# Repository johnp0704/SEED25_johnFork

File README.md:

# The Autonomous Weeding Garden Robot (AWGR)

[User operation video](https://drive.google.com/file/d/1jZLO9X0hrXnLbDT-zOZEFcToG8p_CPjy/view?usp=sharing) <br/>
There are a number of folders in this repo to help develop the AWGR. There are README files in each directory with further clarification of individual files. 
## RC Control 
Guide on how to setup RC mode for the robot. Scripts for microcontrollers.
## automation 
Guide for the robots autonomy. Includes information on the script that runs on startup, and the script itself. 
## drawings
.png files of all the parts that were either 3D printed or machined for the robot. does not contain a README because it is just pictures.
## schematics_and_drawings
Similar to the above, including all the solidworks files for each assembly. Ask your mechanical engineer. Also includes the electrical wiring diagram. 
## some_examples 
Files that we used for development and understanding of Jetson GPIO, realsense, serial communications, etc. The README in there describes how to run each example. 
## training 
Guide for training the neural network that the machine will use to discern between weeds and plants. Contains some README information from [roboflow](https://app.roboflow.com) that is helpful in creating a database for the training algorithm to use.

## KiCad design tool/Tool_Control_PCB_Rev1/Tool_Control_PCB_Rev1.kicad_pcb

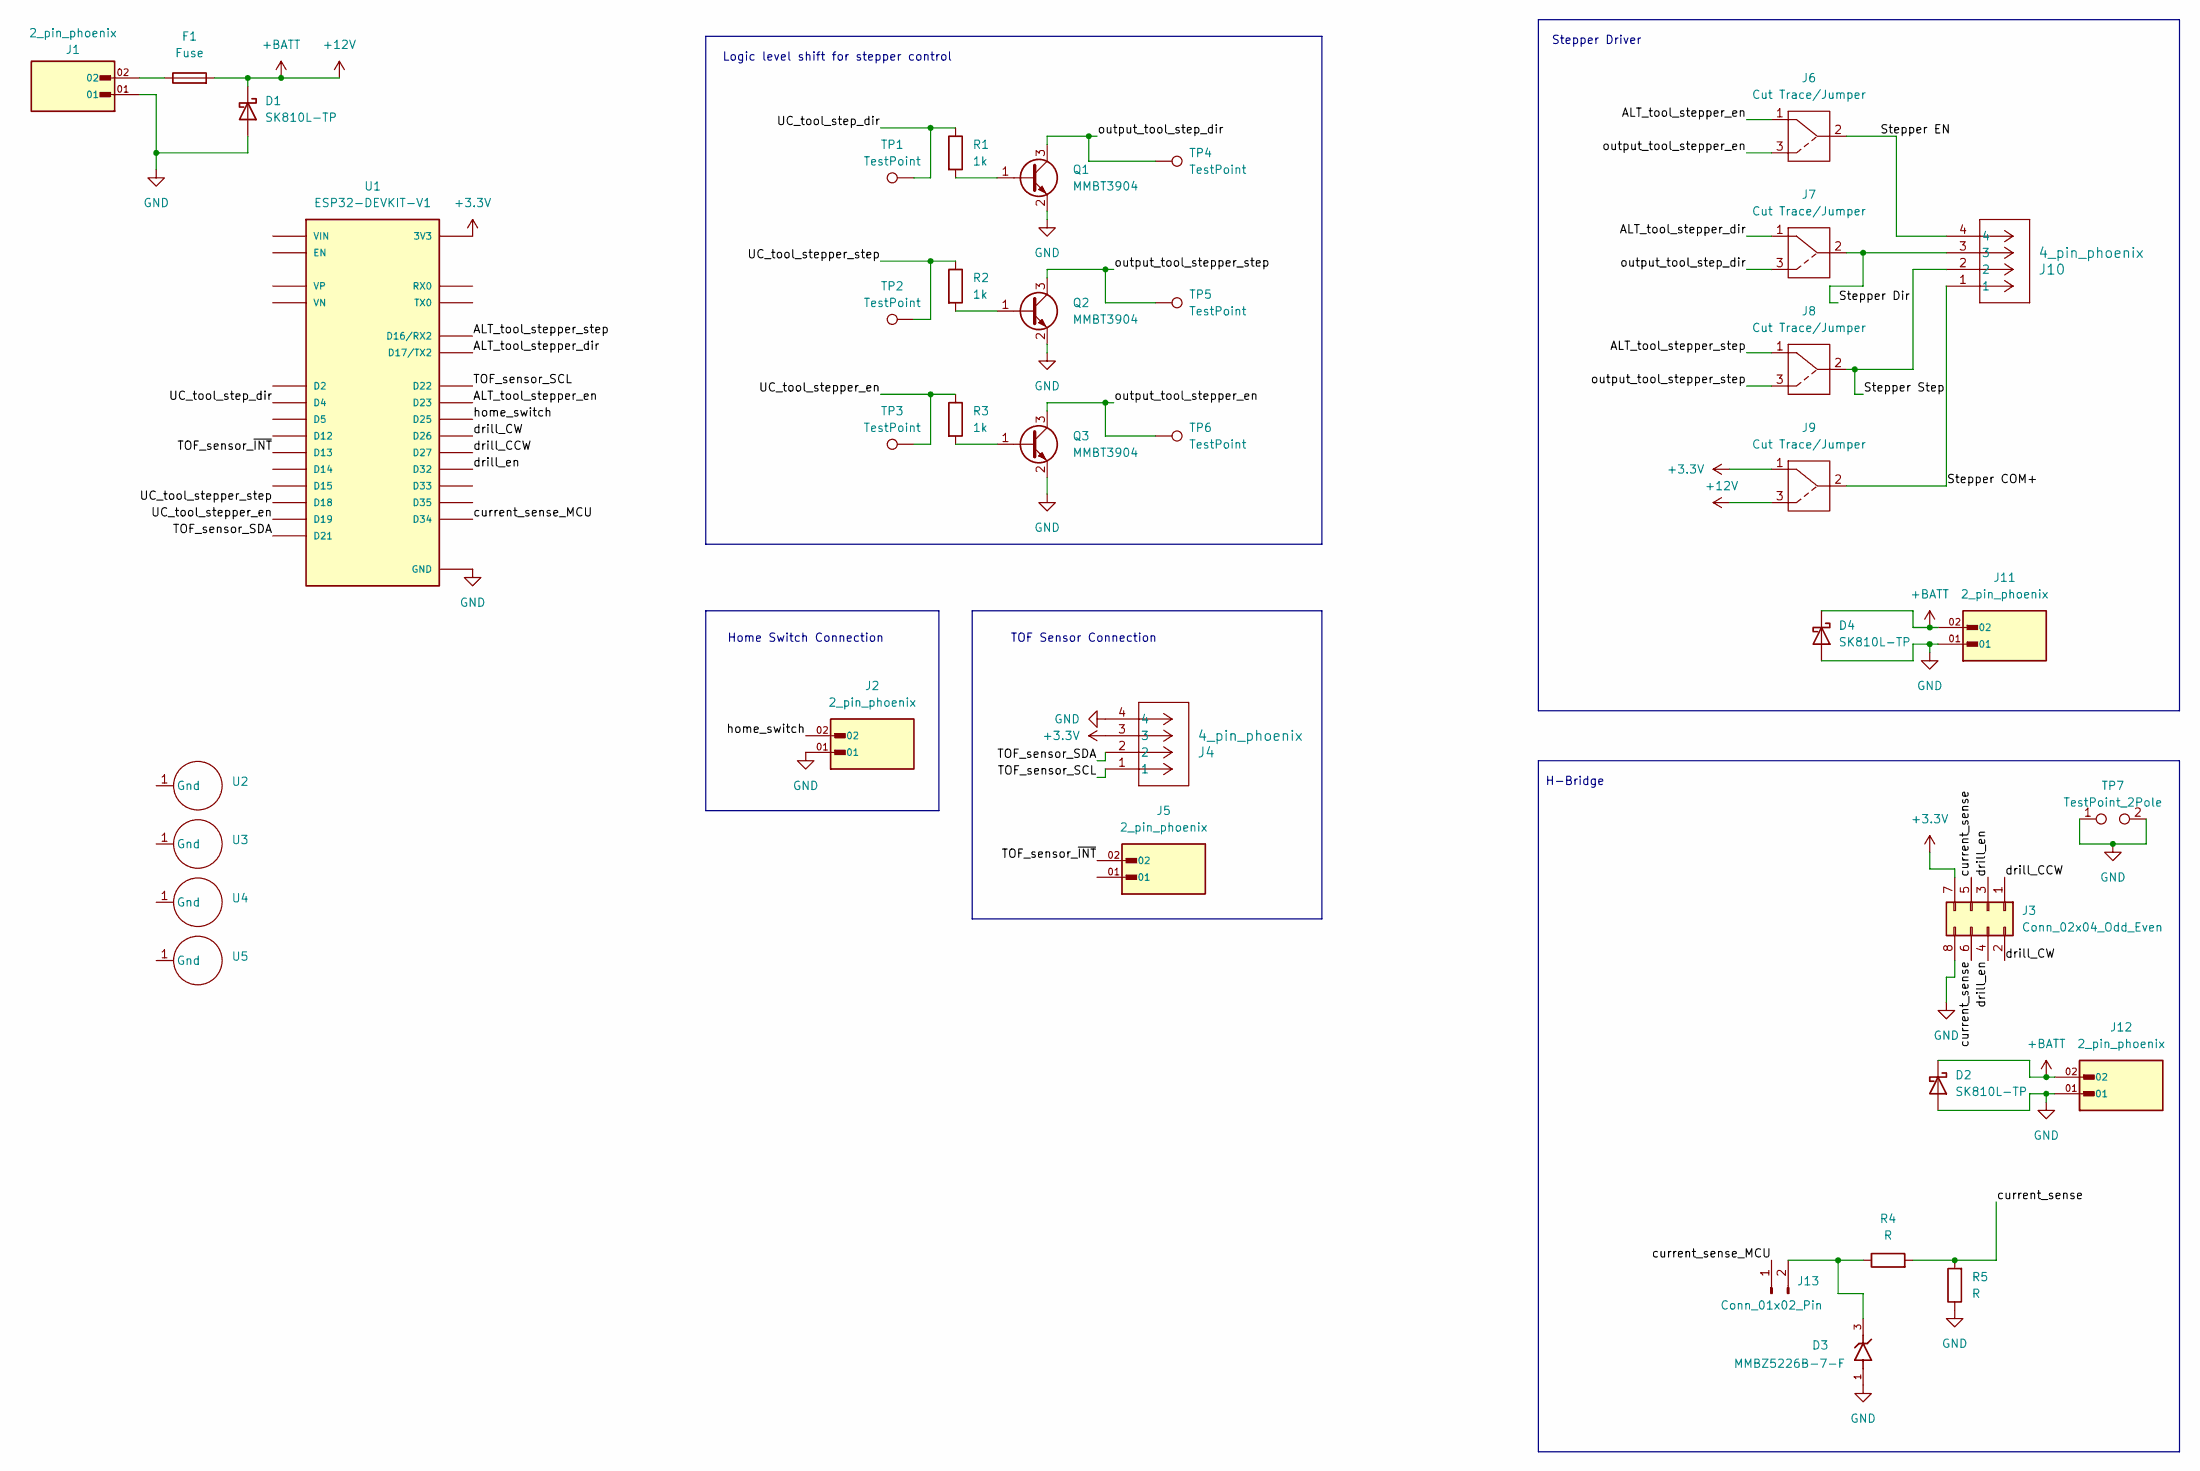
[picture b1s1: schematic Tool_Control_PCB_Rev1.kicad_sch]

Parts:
D1, D2, D4: SK810L-TP; D_SMC_Handsoldering
D3: MMBZ5226B-7-F; SOT91P240X102-3N
F1: Fuse; 01530008 (FuseHold)
J1, J2, J5, J11, J12: 2_pin_phoenix; PHOENIX_1757242; PARTREV 28.07.2023; DigiKey_Part_Number 277-1106-ND
J3: Conn_02x04_Odd_Even; PinHeader_2x04_P2.54mm_Vertical
J4, J10: 4_pin_phoenix; CONN_1757268_PXC
J6, J7, J8, J9: Cut Trace/Jumper; Jumper Selector
J13: Conn_01x02_Pin; PinHeader_1x02_P2.54mm_Vertical
Q1, Q2, Q3: MMBT3904; SOT-23
R1, R2, R3: 1k; R_1206_3216Metric_Pad1.30x1.75mm_HandSolder
R4, R5: R; R_1206_3216Metric_Pad1.30x1.75mm_HandSolder
TP1, TP2, TP3, TP4, TP5, TP6: TestPoint; TestPoint_Pad_D3.0mm
TP7: TestPoint_2Pole; Ground_Point
U1: ESP32-DEVKIT-V1; MODULE_ESP32_DEVKIT_V1; PARTREV N/A
U2, U3, U4, U5: M3 bolt

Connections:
+3.3V: J3.7, J4.3, J9.1, U1.1 (3V3)
+12V: D1.1 (K), D2.1 (K), D4.1 (K), F1.2, J9.3, J11.02, J12.02
/ALT_tool_stepper_dir: J7.1, U1.7 (D17/TX2)
/ALT_tool_stepper_en: J6.1, U1.15 (D23)
/ALT_tool_stepper_step: J8.1, U1.6 (D16/RX2)
/Stepper COM+: J9.2, J10.1
/Stepper Dir: J7.2, J10.3
/Stepper EN: J6.2, J10.4
/Stepper Step: J8.2, J10.2
/TOF_sensor_SCL: J4.1, U1.14 (D22)
/TOF_sensor_SDA: J4.2, U1.11 (D21)
/TOF_sensor_~INT: J5.02, U1.28 (D13)
/UC_tool_step_dir: R1.1, TP1.1, U1.5 (D4)
/UC_tool_stepper_en: R3.1, TP3.1, U1.10 (D19)
/UC_tool_stepper_step: R2.1, TP2.1, U1.9 (D18)
/current_sense: J3.5, J3.6, R4.2, R5.2
/current_sense_MCU: J13.1, U1.19 (D34)
/drill_CCW: J3.1, U1.25 (D27)
/drill_CW: J3.2, U1.24 (D26)
/drill_en: J3.3, J3.4, U1.21 (D32)
/home_switch: J2.02, U1.23 (D25)
/output_tool_step_dir: J7.3, Q1.3 (C), TP4.1
/output_tool_stepper_en: J6.3, Q3.3 (C), TP6.1
/output_tool_stepper_step: J8.3, Q2.3 (C), TP5.1
GND: D1.2 (A), D2.2 (A), D3.1, D4.2 (A), J1.01, J2.01, J3.8, J4.4, J11.01, J12.01, Q1.2 (E), Q2.2 (E), Q3.2 (E), R5.1, TP7.1, TP7.2, U1.2 (GND), U1.29 (GND)
unnamed: F1.1, J1.02
unnamed: D3.3, J13.2, R4.1
unnamed: Q1.1 (B), R1.2
unnamed: Q2.1 (B), R2.2
unnamed: Q3.1 (B), R3.2

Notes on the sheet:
Home Switch Connection
Stepper Driver
TOF Sensor Connection
H-Bridge
Logic level shift for stepper control

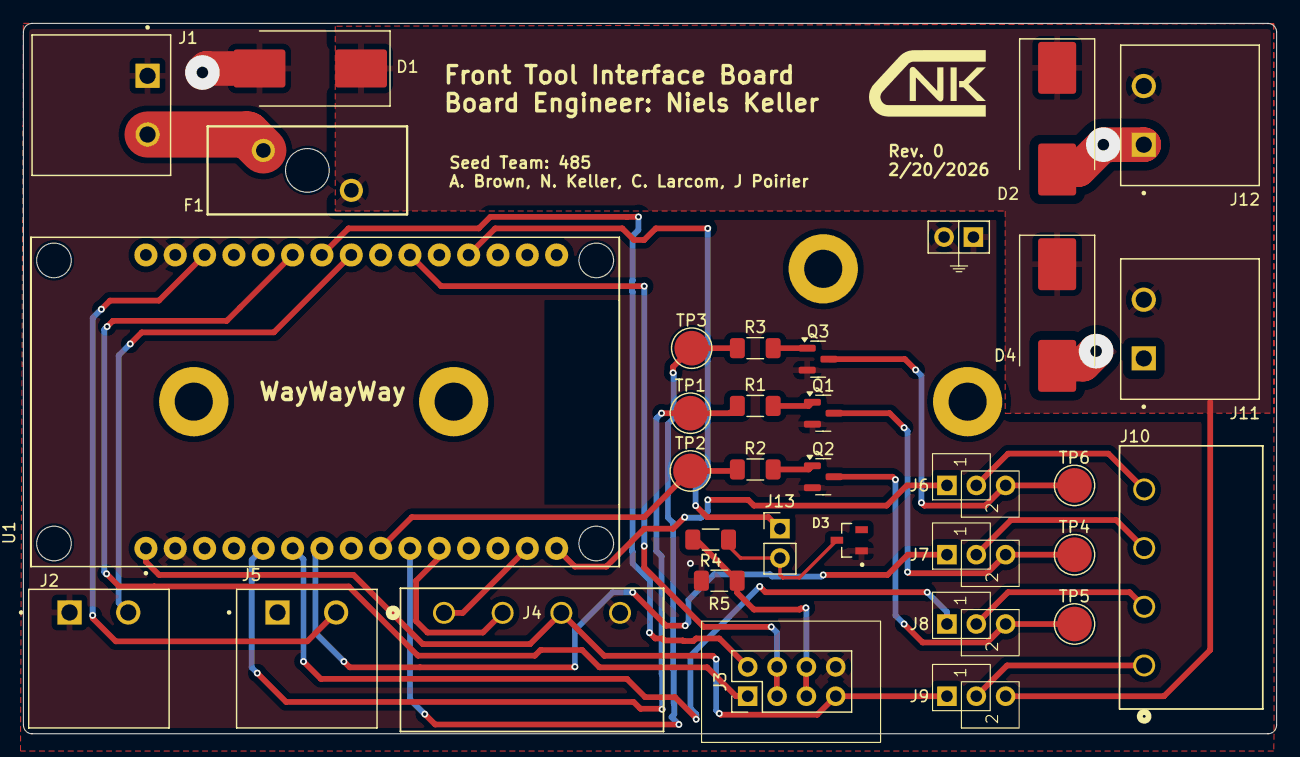
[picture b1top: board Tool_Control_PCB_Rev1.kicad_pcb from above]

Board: 2 copper layers, 108.5 x 61.5 mm, 38 parts (0 on the bottom side), 30 nets.

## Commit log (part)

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2025-11-07 Updated marker index
2025-11-07 updated index var type when checking for goal
2025-11-07 update debug text
2025-11-07 Fixed the way we were pulling marker position data
2025-11-08 Updated gtg node to include gtg
2025-11-08 Fixed conflicting var names
2025-11-08 Fixed arctan typo
2025-11-08 made sure to pass in motor object to controller node
2025-11-08 Added threshold and updated controller consts
2025-11-08 update gains
2025-11-08 edit gains
2025-11-08 update gains and logging
2025-11-08 Unit Fix
2025-11-08 update gains rotation
2025-11-08 Update max speed var
2025-11-08 Added debugging of wl/wr_des before clipping
2025-11-08 Added turning authority logic
2025-11-08 Debuggin by seeing scaled factor
2025-11-08 Fixed L var units
2025-11-08 Updated angle thresh and gains
2025-11-08 updated clippling logic
2025-11-08 Update actuator limits
2025-11-08 Update logging
2025-11-08 Unwrap input angle
2025-11-08 gains update
2025-11-08 Created a mathematical implementation of angle rather than getting from optitrack
2025-11-08 Added alternative angle tracking node
2025-11-08 Make sure to check to wait till the controller gets maker data
2025-11-08 added msg dumping for debug
2025-11-08 fixed logic
2025-11-08 Making sure to look in right place for marker data
2025-11-08 update where to look for ridged body markers
2025-11-08 update marker loc
2025-11-08 flip unit vector
2025-11-08 fix tuple var
2025-11-08 flip unit vector properly
2025-11-09 File Organization
2025-11-09 Added DETR Model
2025-11-10 Add telemetry node
2025-11-10 Fixed file name
2025-11-10 Created automatic data splitting script for YOLO
2025-11-10 Changed file organization of images
2025-11-10 Changed rigid body heading vector finding
2025-11-10 Added angle softening
2025-11-10 Added plotting, changed gtg node
2025-11-10 Fixed plotting and gtg nodes
2025-11-10 Updated potting and gtg controller
2025-11-10 Updated to plot and gtg
2025-11-11 Changed File Organization
2025-11-11 Fixed file organization
2025-11-11 Incredible YOLO model created
2025-11-12 Started new controller
2025-11-12 change print type
2025-11-12 add goal logging
2025-11-12 add telemetry
2025-11-12 fix typo in controller
2025-11-12 second typo
2025-11-12 added logging
2025-11-12 typo
2025-11-12 update plotting
2025-11-12 fix plotting
2025-11-12 Fix quaternion rotation offset
2025-11-12 Fix rotation by adding 90 degree offset
2025-11-12 fix direction
2025-11-12 Update telemetry
2025-11-12 stop clearing textbox
2025-11-12 Fixed text/legends Plotting
2025-11-12 fix typo
2025-11-12 Make telem faster
2025-11-12 fix telem
2025-11-12 test telem
2025-11-12 first test of rest of controller
2025-11-12 Split telemetry and gtg into two nodes
2025-11-12 fixed typo in setup
2025-11-12 fixed setup again
2025-11-12 Update telem and controller logic
2025-11-12 fix telem 2
2025-11-12 fix turn logic
2025-11-12 gains/treshs
2025-11-12 gains + thres
2025-11-21 Added Wave 6 and 8 Annotations
2025-11-21 Wave 7
2025-11-21 Add Git LFS tracking for large files
2025-11-21 COCO Waves 2 & 7
2025-11-21 DETR Additions
2025-11-21 Added COCO wave 1, 4, 6 annotations
2025-11-21 DETR Changes
2025-11-22 More DETR Modifications
2025-12-05 Added XGBoost annotations for waves 1, 4, 6, 8
2025-12-05 Fixed confusion matrix
2025-12-06 Revert "Merge pull request #14 from johnp0704/main"
    This reverts commit 8882b1b695f7f94a4a517552ff939409ce4e83a0, reversing
    changes made to 599f16532e06215caf6500b54fceb1b4f0b7fc44.
    Update Images/Testing Annotated/YOLOTestingAnnotations/Data/images/test/photo_20251017_1003.png
    Update Images/Testing Annotated/YOLOTestingAnnotations/Data/images/test/photo_20251017_1004.png
    Update Images/Testing Annotated/YOLOTestingAnnotations/Data/images/test/photo_20251017_1027.png
    Update Images/Testing Annotated/YOLOTestingAnnotations/Data/images/test/photo_20251017_1036.png
2025-12-06 Stop tracking Data folder
2025-12-06 Added data folder to git ignore, prevent large file commits
2025-12-06 Re-training YOLO
2025-12-06 Re-trained YOLO pt 1
2025-12-06 Retrained YOLO pt2
2025-12-06 Retrained YOLO pt3
2025-12-06 YOLO is fr done now I'm done wit it fr fr done wit ts
2025-12-07 Added files for Logistic Regression
2025-12-07 Added DETR wave 8 annotations
2025-12-07 XGBoost
2025-12-07 logistic regression labels
2025-12-07 File naming
2025-12-07 File organizing
2025-12-07 XGBoost update
2025-12-07 XGBoost model
2025-12-07 Fixed some files
2025-12-07 Fixed file names
2025-12-07 DETR split changes
2025-12-07 DETR split update
2025-12-07 Minor changes
2025-12-07 Added DETR split to git ignroe
2025-12-07 Restored changes
2025-12-07 DETR training changes
2025-12-07 Set for John PC
2025-12-07 DETR training optimization
2025-12-07 Changed DETR to
2025-12-07 Updated to use John desktop
2025-12-07 Updates to DETR
2025-12-07 DETR things
2025-12-07 DETR stuff
2025-12-07 DETR
2025-12-07 untrack DETR models
2025-12-07 Fixed gitignore
2025-12-07 This shouldn't be tracking.
2025-12-07 Bunch of DETR
2025-12-07 Fixed DETR
2025-12-08 Added DETR CM
2025-12-08 DETR finalizing
2025-12-08 Fixing organization
2025-12-08 Changed ogranization
2025-12-08 Added CM pngs
2025-12-08 Edited for presentation use on laptop
2025-12-08 Update XGBoost
2025-12-08 edits
2025-12-08 Various fixes
2025-12-08 XGBoost fixes
2025-12-08 YOLO fixes
2025-12-08 Created README
2025-12-16 Added report
2026-01-14 Added live video feed detectioin testing
2026-01-14 Red square images
2026-01-14 Red square depth (useless)
2026-01-14 Updated gains and angle thresh
2026-01-23 Red model
2026-01-25 detection
2026-01-26 start of code for tool firmware
2026-01-26 Folder Organization
2026-01-26 BEV and Red Detection
2026-01-27 fixed trapezoidal speed curve
2026-02-02 Adding MV GTG
2026-02-02 MV GTG Changes
2026-02-02 Position tuning
2026-02-06 ros workspace setup
2026-02-09 worked on pcb for tool control
2026-02-10 PCB work on out of board connections
2026-02-13 pin numbering and board changes
2026-02-17 Finished schematic capture and started board layout
2026-02-17 YOLOred
2026-02-20 pre review board
2026-02-20 rev 0 draft
2026-02-21 Submittion of board
2026-02-23 start second tool
2026-03-02 New Package Setup
2026-03-02 Added ROS pkg files
2026-03-02 Added launch file
2026-03-02 Fixing files for Remote Host
2026-03-02 Started working/testing on ESP32 compiler
2026-03-02 Migrated YOLO and GTG scripts to modular ROS 2 architecture on Jetson
2026-03-23 Created optitrack waypoint navigation package
2026-03-23 I messed it up.
2026-03-23 I did it right this time
2026-03-23 Added nodes
2026-03-23 Updated launch file
2026-03-23 setting up optitrack waypoint nav package
2026-03-23 Added camera view to waypoint nav
2026-03-23 Trying to fix this.
2026-03-23 front tool firmware work
2026-03-31 New package
2026-03-31 Packages
2026-03-31 its something
2026-04-01 Trying to fix virtual twin
2026-04-01 Update for calibration
2026-04-01 Updated rigid body index
2026-04-03 changed rigid body index
2026-04-03 Fixed rigid body index
2026-04-03 Tool Firmware rev0
2026-04-03 updated wayponits
2026-04-07 creating motor tester
2026-04-07 Changed various waypoint behavior
2026-04-07 retry
2026-04-07 Changed path following behavior
2026-04-07 Tuning speed and thresholds
2026-04-07 Added spline interpolation
2026-04-16 A whole bunch of things, mostly just stuff for Poster
2026-04-16 Same stuff from Poster
2026-04-16 Updates to firmware
2026-04-18 remote control package
2026-04-18 simple teleop
2026-04-18 I don't remember what I changed
2026-04-19 Using trapezoidal profile for motor controller for smoother starts and stops
2026-04-19 Tuning
2026-04-19 Fixing waypoint manager
2026-04-19 trying to fix
2026-04-21 recalibrating BEV
2026-04-22 Go-to-Goal
2026-04-22 A whole bunch
2026-04-22 adrucam calibration
2026-04-22 recalibrated
2026-04-22 Additions
2026-04-23 creating demo night package
2026-04-23 aruco codes generated
2026-04-23 Updated all pipelines for demo_night package
2026-04-23 do drill no pwm
2026-04-23 dead reckoning calibration
2026-04-23 dead-reckoning calibration
2026-04-23 bev data
2026-04-23 setup and launch files
2026-04-23 Necessary fixes to get compatibility with python 3.8
2026-04-24 i'm trying.
2026-04-24 quick typo fixes
2026-04-24 fixed commander
2026-04-24 Changed arducam ownership
2026-04-24 i dont think this is anything
2026-04-24 more changes
2026-04-24 changing rehome behavior
2026-04-24 hopefully nothing?
2026-04-24 tool
2026-04-24 should be nothing
2026-04-25 I hate this and myself
